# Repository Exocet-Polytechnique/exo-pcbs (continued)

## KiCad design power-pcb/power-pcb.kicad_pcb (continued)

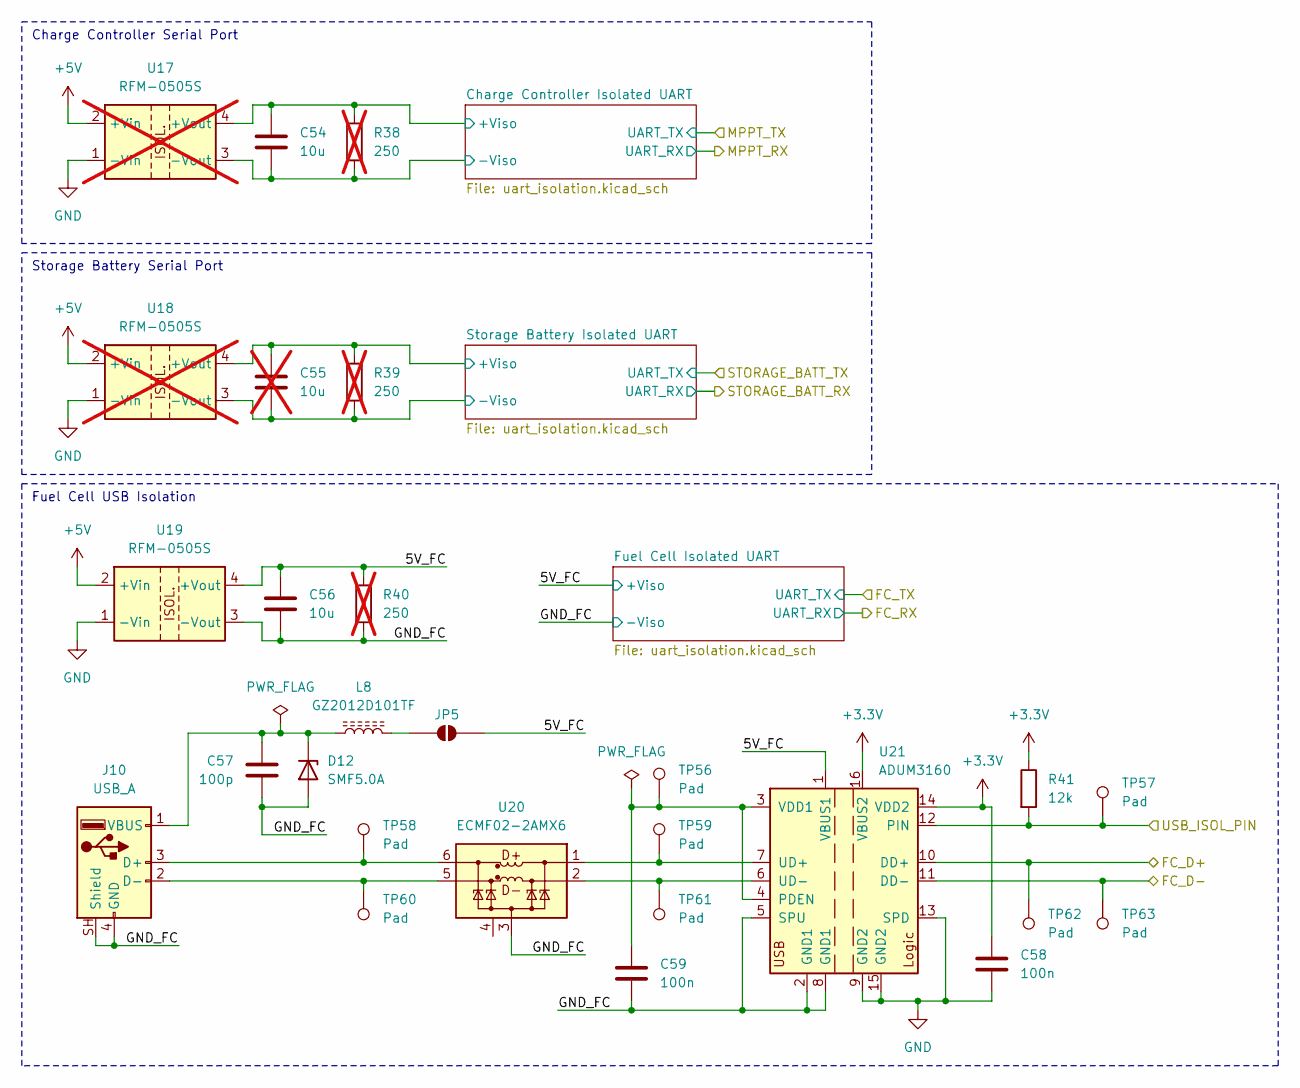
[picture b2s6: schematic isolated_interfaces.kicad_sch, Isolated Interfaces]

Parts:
C54, C56: 10u; C_1206_3216Metric_Pad1.33x1.80mm_HandSolder; JLCPCB C13585
C55: 10u; C_1206_3216Metric_Pad1.33x1.80mm_HandSolder; JLCPCB C13585; not fitted
C57: 100p; C_0402_1005Metric_Pad0.74x0.62mm_HandSolder; JLCPCB C1546
C58, C59: 100n; C_0402_1005Metric_Pad0.74x0.62mm_HandSolder; JLCPCB C307331
D12: SMF5.0A; D_SOD-123F; JLCPCB C19077497
J10: USB_A; USB_A_Molex_67643_Horizontal; MPN 0676430910
JP5: SolderJumper_2_Open; SolderJumper-2_P1.3mm_Open_RoundedPad1.0x1.5mm
L8: GZ2012D101TF; L_0805_2012Metric_Pad1.05x1.20mm_HandSolder; JLCPCB C1015
R38, R39, R40: 250; R_Axial_DIN0309_L9.0mm_D3.2mm_P12.70mm_Horizontal; MPN MFR-25FTE52-270R; not fitted
R41: 12k; R_0402_1005Metric_Pad0.72x0.64mm_HandSolder; JLCPCB C25752
TP56, TP57, TP58, TP59, TP60, TP61, TP62, TP63: Pad; TestPoint_Pad_D1.5mm
U17, U18: RFM-0505S; RECOM_SIP-4; MPN RFM-0505S; not fitted
U19: RFM-0505S; RECOM_SIP-4; MPN RFM-0505S
U20: ECMF02-2AMX6; ST_UQFN-6L_1.5x1.7mm_P0.5mm; JLCPCB C2651144
U21: ADUM3160; SOIC-16W_7.5x10.3mm_P1.27mm; MPN ADUM3160BRWZ; JLCPCB C284149

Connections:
+3.3V: C58.1, R41.1, U21.14 (VDD2), U21.16 (VBUS2); also elsewhere on the board
+5V: U17.2 (+Vin), U18.2 (+Vin), U19.2 (+Vin); also elsewhere on the board
/Isolated Interfaces/5V_FC: C56.1, JP5.2 (B), R40.1, U19.4 (+Vout), U21.1 (VBUS1); also elsewhere on the board
/Isolated Interfaces/Charge Controller Isolated UART/+Viso: C54.1, R38.1, U17.4 (+Vout); also elsewhere on the board
/Isolated Interfaces/Charge Controller Isolated UART/-Viso: C54.2, R38.2, U17.3 (-Vout); also elsewhere on the board
/Isolated Interfaces/FC_D+: TP62.1 (1_1), U21.10 (DD+); also elsewhere on the board
/Isolated Interfaces/FC_D-: TP63.1 (1_1), U21.11 (DD-); also elsewhere on the board
/Isolated Interfaces/GND_FC: C56.2, C57.2, C59.2, D12.2 (A), J10.4 (GND), J10.SH (Shield), R40.2, U19.3 (-Vout), U20.3 (GND), U21.2 (GND1), U21.5 (SPU), U21.8 (GND1); also elsewhere on the board
/Isolated Interfaces/Storage Battery Isolated UART/+Viso: C55.1, R39.1, U18.4 (+Vout); also elsewhere on the board
/Isolated Interfaces/Storage Battery Isolated UART/-Viso: C55.2, R39.2, U18.3 (-Vout); also elsewhere on the board
/Isolated Interfaces/USB_ISOL_PIN: R41.2, TP57.1 (1_1), U21.12 (PIN); also elsewhere on the board
GND: C58.2, U17.1 (-Vin), U18.1 (-Vin), U19.1 (-Vin), U21.9 (GND2), U21.13 (SPD), U21.15 (GND2); also elsewhere on the board
unnamed: C57.1, D12.1 (K), J10.1 (VBUS), L8.1
unnamed: J10.3 (D+), TP58.1 (1_1), U20.6 (D+_out)
unnamed: J10.2 (D-), TP60.1 (1_1), U20.5 (D-_out)
unnamed: JP5.1 (A), L8.2
unnamed: TP59.1 (1_1), U20.1 (D+_in), U21.7 (UD+)
unnamed: TP61.1 (1_1), U20.2 (D-_in), U21.6 (UD-)
unnamed: C59.1, TP56.1 (1_1), U21.3 (VDD1), U21.4 (PDEN)

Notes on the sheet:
Storage Battery Serial Port
Charge Controller Serial Port
Fuel Cell USB Isolation

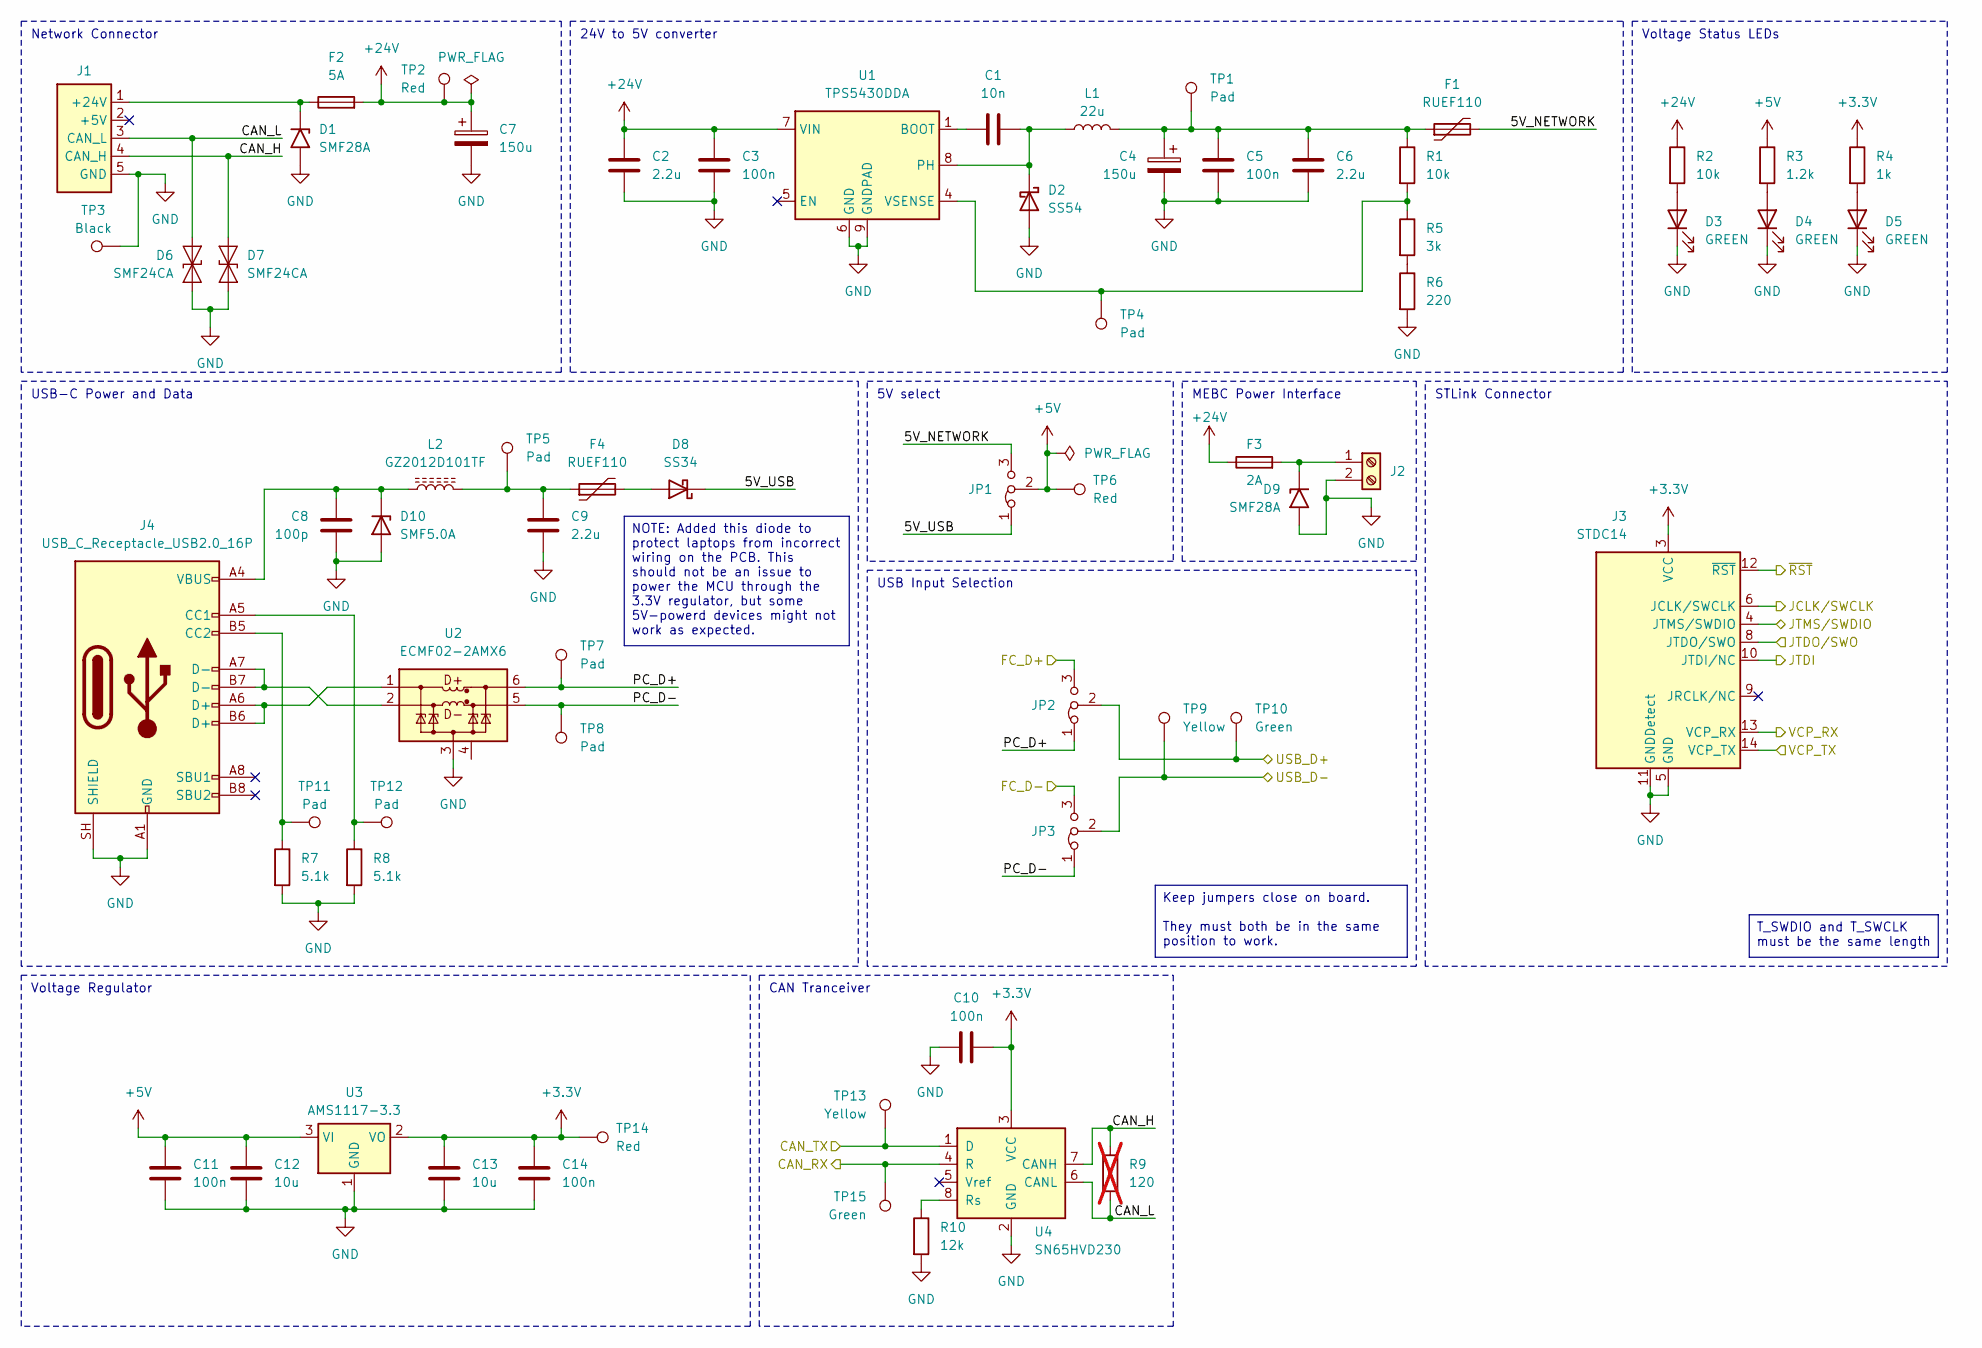
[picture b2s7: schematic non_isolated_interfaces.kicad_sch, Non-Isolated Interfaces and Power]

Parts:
C1: 10n; C_0402_1005Metric_Pad0.74x0.62mm_HandSolder; JLCPCB C15195
C2, C6, C9: 2.2u; C_0805_2012Metric_Pad1.18x1.45mm_HandSolder; JLCPCB C377773
C3, C5, C10, C11, C14: 100n; C_0402_1005Metric_Pad0.74x0.62mm_HandSolder; JLCPCB C307331
C4, C7: 150u; CP_Radial_D8.0mm_P3.50mm; MPN 860020574010
C8: 100p; C_0402_1005Metric_Pad0.74x0.62mm_HandSolder; JLCPCB C1546
C12, C13: 10u; C_1206_3216Metric_Pad1.33x1.80mm_HandSolder; JLCPCB C13585
D1, D9: SMF28A; D_SMF; JLCPCB C41376091
D2: SS54; D_SMA_Handsoldering; JLCPCB C22452
D3, D4, D5: GREEN; LED_0805_2012Metric_With_Annotations; JLCPCB C2297
D6, D7: SMF24CA; D_SOD-123F; JLCPCB C19077515
D8: SS34; D_SMA; JLCPCB C8678
D10: SMF5.0A; D_SOD-123F; JLCPCB C19077497
F1, F4: RUEF110; Fuse_Littelfuse_395Series; MPN RUEF110
F2: 5A; Fuseholder_Littelfuse_Combined; MPN 01110501Z
F3: 2A; Fuseholder_Littelfuse_Combined; MPN 01110501Z
J1: Network Connector; Molex_SPOX_5268-05A_1x05_P2.50mm_Horizontal; MPN 0022057055
J2: Screw_Terminal_01x02; Wuerth_Term_Blk_2pos_Side_Entry_5mm; MPN 691137710002
J3: STDC14; PinHeader_2x07_P1.27mm_Vertical_SMD; JLCPCB C7465995
J4: USB_C_Receptacle_USB2.0_16P; USB_C_Receptacle_GCT_USB4085; MPN USB4920-00-A
JP1, JP2, JP3: Jumper_3_Bridged12; PinHeader_1x03_P2.54mm_Vertical; MPN PR20203VBNN
L1: 22u; L_Axial_L16.0mm_D6.3mm_P5.08mm_Vertical_Fastron_VHBCC; MPN AIAP-02-220K
L2: GZ2012D101TF; L_0805_2012Metric_Pad1.05x1.20mm_HandSolder; JLCPCB C1015
R1, R2: 10k; R_0805_2012Metric_Pad1.20x1.40mm_HandSolder; JLCPCB C17414
R3: 1.2k; R_0603_1608Metric_Pad0.98x0.95mm_HandSolder; JLCPCB C22765
R4: 1k; R_0603_1608Metric_Pad0.98x0.95mm_HandSolder; JLCPCB C21190
R5: 3k; R_0603_1608Metric_Pad0.98x0.95mm_HandSolder; JLCPCB C4211
R6: 220; R_0402_1005Metric_Pad0.72x0.64mm_HandSolder; JLCPCB C25091
R7, R8: 5.1k; R_0402_1005Metric_Pad0.72x0.64mm_HandSolder; JLCPCB C25905
R9: 120; R_Axial_DIN0309_L9.0mm_D3.2mm_P12.70mm_Horizontal; MPN CF12JT120R; not fitted
R10: 12k; R_0402_1005Metric_Pad0.72x0.64mm_HandSolder; JLCPCB C25752
TP1, TP4, TP5, TP7, TP8, TP11, TP12: Pad; TestPoint_Pad_D1.5mm
TP2, TP6, TP14: Red; TestPoint_Keystone_5005-5009_Compact; MPN 5005
TP3: Black; TestPoint_Keystone_5005-5009_Compact; MPN 5006
TP9, TP13: Yellow; TestPoint_Keystone_5005-5009_Compact; MPN 5009
TP10, TP15: Green; TestPoint_Keystone_5005-5009_Compact; MPN 5121
U1: TPS5430DDA; TI_SO-PowerPAD-8_ThermalVias; JLCPCB C9864
U2: ECMF02-2AMX6; ST_UQFN-6L_1.5x1.7mm_P0.5mm; JLCPCB C2651144
U3: AMS1117-3.3; SOT-223-3_TabPin2; JLCPCB C6186
U4: SN65HVD230; SOIC-8_3.9x4.9mm_P1.27mm; JLCPCB C12084

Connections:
+3.3V: C10.1, C13.1, C14.1, J3.3 (VCC), R4.1, TP14.1 (1_1), U3.2 (VO), U4.3 (VCC); also elsewhere on the board
+5V: C11.1, C12.1, JP1.2 (C), R3.1, TP6.1 (1_1), U3.3 (VI); also elsewhere on the board
+24V: C2.2, C3.1, C7.1, F2.2, F3.1, R2.1, TP2.1 (1_1), U1.7 (VIN); also elsewhere on the board
/Isolated Interfaces/FC_D+: JP2.3 (B); also elsewhere on the board
/Isolated Interfaces/FC_D-: JP3.3 (B); also elsewhere on the board
/Non-Isolated Interfaces and Power/5V_NETWORK: F1.2, JP1.3 (B)
/Non-Isolated Interfaces and Power/5V_USB: D8.1 (K), JP1.1 (A)
/Non-Isolated Interfaces and Power/CAN_H: D7.2 (A2), J1.4 (CAN_H), R9.1, U4.7 (CANH)
/Non-Isolated Interfaces and Power/CAN_L: D6.2 (A2), J1.3 (CAN_L), R9.2, U4.6 (CANL)
/Non-Isolated Interfaces and Power/CAN_RX: TP15.1 (1_1), U4.4 (R); also elsewhere on the board
/Non-Isolated Interfaces and Power/CAN_TX: TP13.1 (1_1), U4.1 (D); also elsewhere on the board
/Non-Isolated Interfaces and Power/JCLK/SWCLK: J3.6 (JCLK/SWCLK); also elsewhere on the board
/Non-Isolated Interfaces and Power/JTDI: J3.10 (JTDI/NC); also elsewhere on the board
/Non-Isolated Interfaces and Power/JTDO/SWO: J3.8 (JTDO/SWO); also elsewhere on the board
/Non-Isolated Interfaces and Power/JTMS/SWDIO: J3.4 (JTMS/SWDIO); also elsewhere on the board
/Non-Isolated Interfaces and Power/PC_D+: JP2.1 (A), TP7.1 (1_1), U2.6 (D+_out)
/Non-Isolated Interfaces and Power/PC_D-: JP3.1 (A), TP8.1 (1_1), U2.5 (D-_out)
/Non-Isolated Interfaces and Power/USB_D+: JP2.2 (C), TP10.1 (1_1); also elsewhere on the board
/Non-Isolated Interfaces and Power/USB_D-: JP3.2 (C), TP9.1 (1_1); also elsewhere on the board
/Non-Isolated Interfaces and Power/VCP_RX: J3.13 (VCP_RX); also elsewhere on the board
/Non-Isolated Interfaces and Power/VCP_TX: J3.14 (VCP_TX); also elsewhere on the board
/Non-Isolated Interfaces and Power/~RST: J3.12 (~RST); also elsewhere on the board
GND: C2.1, C3.2, C4.2, C5.2, C6.1, C7.2, C8.2, C9.2, C10.2, C11.2, C12.2, C13.2, C14.2, D1.2 (A2), D2.2 (A), D3.1 (K), D4.1 (K), D5.1 (K), D6.1 (A1), D7.1 (A1), D9.2 (A2), D10.2 (A), J1.5 (GND), J2.2, J3.5 (GND), J3.7 (GND), J3.11 (GNDDetect), J4.A1 (GND), J4.A12 (GND), J4.B1 (GND), J4.B12 (GND), J4.SH (SHIELD), R6.2, R7.2, R8.2, R10.2, TP3.1 (1_1), U1.6 (GND), U1.9 (GNDPAD), U2.3 (GND), U3.1 (GND), U4.2 (GND); also elsewhere on the board
unnamed: C4.1, C5.1, C6.2, F1.1, L1.2, R1.1, TP1.1 (1_1)
unnamed: C9.1, F4.1, L2.2, TP5.1 (1_1)
unnamed: D1.1 (A1), F2.1, J1.1 (+24V)
unnamed: C1.2, D2.1 (K), L1.1, U1.8 (PH)
unnamed: D3.2 (A), R2.2
unnamed: D4.2 (A), R3.2
unnamed: D5.2 (A), R4.2
unnamed: D8.2 (A), F4.2
unnamed: D9.1 (A1), F3.2, J2.1
unnamed: C8.1, D10.1 (K), J4.A4 (VBUS), J4.A9 (VBUS), J4.B4 (VBUS), J4.B9 (VBUS), L2.1
unnamed: J4.A5 (CC1), R8.1, TP12.1 (1_1)
unnamed: J4.B5 (CC2), R7.1, TP11.1 (1_1)
unnamed: R5.2, R6.1
unnamed: C1.1, U1.1 (BOOT)
unnamed: R1.2, R5.1, TP4.1 (1_1), U1.4 (VSENSE)
unnamed: J4.A6 (D+), J4.B6 (D+), U2.1 (D+_in)
unnamed: J4.A7 (D-), J4.B7 (D-), U2.2 (D-_in)
unnamed: R10.1, U4.8 (Rs)

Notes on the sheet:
Voltage Regulator
CAN Tranceiver
5V select
USB-C Power and Data
MEBC Power Interface
USB Input Selection
Network Connector
24V to 5V converter
STLink Connector
Voltage Status LEDs
NOTE: Added this diode to protect laptops from incorrect wiring on the PCB. This should not be an issue to power the MCU through the 3.3V regulator, but some 5V-powerd devices might not work as expected.
T_SWDIO and T_SWCLK must be the same length
Keep jumpers close on board. They must both be in the same position to work.

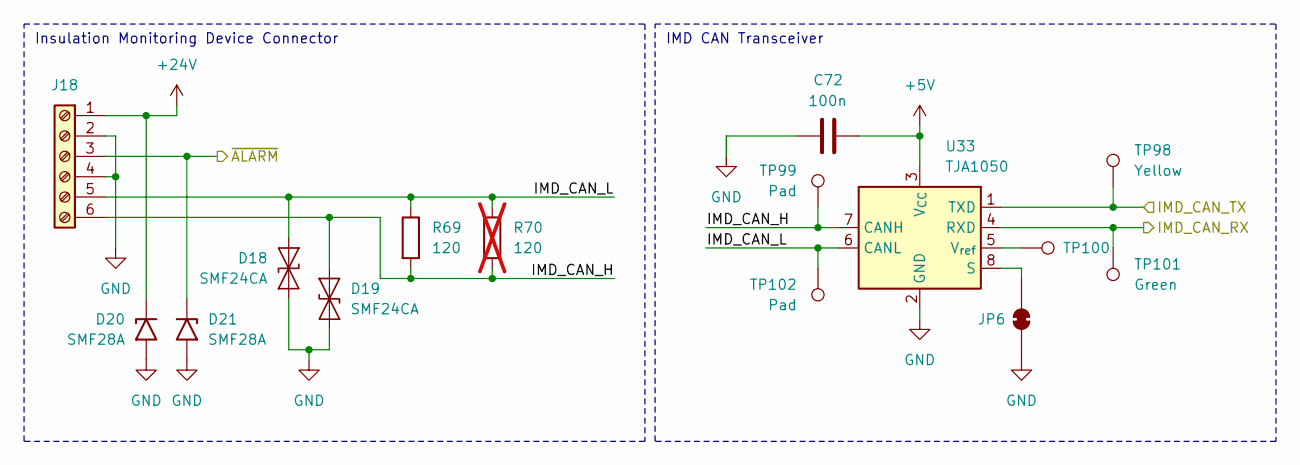
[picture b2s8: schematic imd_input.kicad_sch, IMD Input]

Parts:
C72: 100n; C_0402_1005Metric_Pad0.74x0.62mm_HandSolder; JLCPCB C307331
D18, D19: SMF24CA; D_SOD-123F; JLCPCB C19077515
D20, D21: SMF28A; D_SMF; JLCPCB C41376091
J18: Screw_Terminal_01x06; Wuerth_Term_Blk_6pos_Side_Entry_5mm; MPN 691137710006
JP6: SolderJumper_2_Bridged; SolderJumper-2_P1.3mm_Bridged_Pad1.0x1.5mm
R69: 120; R_Axial_DIN0309_L9.0mm_D3.2mm_P12.70mm_Horizontal; MPN CF12JT120R
R70: 120; R_Axial_DIN0309_L9.0mm_D3.2mm_P12.70mm_Horizontal; MPN CF12JT120R; not fitted
TP98: Yellow; TestPoint_Keystone_5005-5009_Compact; MPN 5009
TP99, TP102: Pad; TestPoint_Pad_D1.5mm
TP100: Hole; TestPoint_THTPad_D2.0mm_Drill1.0mm
TP101: Green; TestPoint_Keystone_5005-5009_Compact; MPN 5121
U33: TJA1050; SOIC-8_3.9x4.9mm_P1.27mm; JLCPCB C6952

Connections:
+5V: C72.2, U33.3 (V_{CC}); also elsewhere on the board
+24V: D20.1 (A1), J18.1; also elsewhere on the board
/STM32 Microcontroller/IMD_CAN_RX: TP101.1 (1_1), U33.4 (RXD); also elsewhere on the board
/STM32 Microcontroller/IMD_CAN_TX: TP98.1 (1_1), U33.1 (TXD); also elsewhere on the board
/Safety Systems/IMD Input/IMD_CAN_H: D19.2 (A2), J18.6, R69.2, R70.2, TP99.1 (1_1), U33.7 (CANH)
/Safety Systems/IMD Input/IMD_CAN_L: D18.2 (A2), J18.5, R69.1, R70.1, TP102.1 (1_1), U33.6 (CANL)
/Safety Systems/~ALARM: D21.1 (A1), J18.3; also elsewhere on the board
GND: C72.1, D18.1 (A1), D19.1 (A1), D20.2 (A2), D21.2 (A2), J18.2, J18.4, JP6.1 (A), U33.2 (GND); also elsewhere on the board
unnamed: JP6.2 (B), U33.8 (S)
unnamed: TP100.1 (1_1), U33.5 (V_{ref})

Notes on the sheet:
Insulation Monitoring Device Connector
IMD CAN Transceiver

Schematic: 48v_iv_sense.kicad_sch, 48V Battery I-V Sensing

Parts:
C40, C41, C42: 100n; C_0402_1005Metric_Pad0.74x0.62mm_HandSolder; JLCPCB C307331
C43, C44, C45, C46: 10n; C_0402_1005Metric_Pad0.74x0.62mm_HandSolder; JLCPCB C15195
J8: Screw_Terminal_01x03; Wuerth_Term_Blk_3pos_Side_Entry_5mm; MPN 691137710003
L4, L5: GZ2012D101TF; L_0805_2012Metric_Pad1.05x1.20mm_HandSolder; JLCPCB C1015
R20: 56k; R_0603_1608Metric_Pad0.98x0.95mm_HandSolder; JLCPCB C23206
R21: 5.1k; R_0402_1005Metric_Pad0.72x0.64mm_HandSolder; JLCPCB C25905
R22, R23, R24, R25: 12k; R_0402_1005Metric_Pad0.72x0.64mm_HandSolder; JLCPCB C25752
R26, R27: 2.7k; R_0603_1608Metric_Pad0.98x0.95mm_HandSolder; JLCPCB C13167
R28: 100; R_0603_1608Metric_Pad0.98x0.95mm_HandSolder; JLCPCB C22775
TP42, TP46, TP48: Hole; TestPoint_THTPad_D2.0mm_Drill1.0mm
TP43, TP45: Pad; TestPoint_Pad_D1.5mm
TP44: Yellow; TestPoint_Keystone_5005-5009_Compact; MPN 5009
TP47: Green; TestPoint_Keystone_5005-5009_Compact; MPN 5121
U9: MCP6002T; SOIC-8_3.9x4.9mm_P1.27mm; MPN MCP6002T-I/SN; JLCPCB C7377
U10: INA240A1D; SOIC-8_3.9x4.9mm_P1.27mm; JLCPCB C2060769
U11: ADS1015IDGS; TSSOP-10_3x3mm_P0.5mm; JLCPCB C193969
U12: ISO1540; SOIC-8_3.9x4.9mm_P1.27mm; JLCPCB C179739

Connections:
+3.3V: U12.1 (VCC1); also elsewhere on the board
/Battery Sensing/Auxiliary Battery I-V Sensing/5V_ISO: C41.1, L4.1, L5.1, R26.1, R27.1, U9.8 (V+), U12.8 (VCC2); also elsewhere on the board
/Battery Sensing/Auxiliary Battery I-V Sensing/ADDR: C40.2, C41.2, C42.2, C43.2, C44.2, C45.2, C46.2, J8.3, R21.1, R23.1, R25.1, R28.1, U9.4 (V-), U10.2 (GND), U10.4 (GND), U10.7 (REF1), U11.3 (GND), U12.5 (GND2); also elsewhere on the board
/Battery Sensing/Auxiliary Battery I-V Sensing/I_SENSE: C43.1, TP43.1 (1_1), U10.5, U11.4 (AIN0)
/Battery Sensing/Auxiliary Battery I-V Sensing/SENSE+: J8.1, R22.1
/Battery Sensing/Auxiliary Battery I-V Sensing/SENSE-: J8.2, R20.1, R24.1
/Battery Sensing/Auxiliary Battery I-V Sensing/V_SENSE: C44.1, TP45.1 (1_1), U9.1, U9.2 (-), U11.5 (AIN1)
/Battery Sensing/SCL: U12.3 (SCL1); also elsewhere on the board
/Battery Sensing/SDA: U12.2 (SDA1); also elsewhere on the board
GND: U12.4 (GND1); also elsewhere on the board
unnamed: TP42.1 (1_1), U9.7
unnamed: R20.2, R21.2, U9.3 (+)
unnamed: R23.2, U9.5 (+)
unnamed: R25.2, U9.6 (-)
unnamed: R22.2, U10.8 (+)
unnamed: R24.2, U10.1 (-)
unnamed: C40.1, L4.2, U10.3 (REF2), U10.6 (V+)
unnamed: R28.2, U11.1 (ADDR)
unnamed: C45.1, TP46.1 (1_1), U11.6 (AIN2)
unnamed: C46.1, TP48.1 (1_1), U11.7 (AIN3)
unnamed: R26.2, TP44.1 (1_1), U11.10 (SCL), U12.6 (SCL2)
unnamed: R27.2, TP47.1 (1_1), U11.9 (SDA), U12.7 (SDA2)
unnamed: C42.1, L5.2, U11.8 (VDD)

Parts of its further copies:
C47, C48, C49: 100n; C_0402_1005Metric_Pad0.74x0.62mm_HandSolder; JLCPCB C307331
C50, C51, C52, C53: 10n; C_0402_1005Metric_Pad0.74x0.62mm_HandSolder; JLCPCB C15195
J9: Screw_Terminal_01x03; Wuerth_Term_Blk_3pos_Side_Entry_5mm; MPN 691137710003
L6, L7: GZ2012D101TF; L_0805_2012Metric_Pad1.05x1.20mm_HandSolder; JLCPCB C1015
R29: 56k; R_0603_1608Metric_Pad0.98x0.95mm_HandSolder; JLCPCB C23206
R30: 5.1k; R_0402_1005Metric_Pad0.72x0.64mm_HandSolder; JLCPCB C25905
R31, R32, R33, R34: 12k; R_0402_1005Metric_Pad0.72x0.64mm_HandSolder; JLCPCB C25752
R35, R36: 2.7k; R_0603_1608Metric_Pad0.98x0.95mm_HandSolder; JLCPCB C13167
R37: 100; R_0603_1608Metric_Pad0.98x0.95mm_HandSolder; JLCPCB C22775
TP49, TP53, TP55: Hole; TestPoint_THTPad_D2.0mm_Drill1.0mm
TP50, TP52: Pad; TestPoint_Pad_D1.5mm
TP51: Yellow; TestPoint_Keystone_5005-5009_Compact; MPN 5009
TP54: Green; TestPoint_Keystone_5005-5009_Compact; MPN 5121
U13: MCP6002T; SOIC-8_3.9x4.9mm_P1.27mm; MPN MCP6002T-I/SN; JLCPCB C7377
U14: INA240A1D; SOIC-8_3.9x4.9mm_P1.27mm; JLCPCB C2060769
U15: ADS1015IDGS; TSSOP-10_3x3mm_P0.5mm; JLCPCB C193969
U16: ISO1540; SOIC-8_3.9x4.9mm_P1.27mm; JLCPCB C179739

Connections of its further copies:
+3.3V: U16.1 (VCC1); also elsewhere on the board
/Battery Sensing/SCL: U16.3 (SCL1); also elsewhere on the board
/Battery Sensing/SDA: U16.2 (SDA1); also elsewhere on the board
/Battery Sensing/Storage Battery I-V Sensing/5V_ISO: C48.1, L6.1, L7.1, R35.1, R36.1, R37.1, U13.8 (V+), U16.8 (VCC2); also elsewhere on the board
/Battery Sensing/Storage Battery I-V Sensing/GND_ISO: C47.2, C48.2, C49.2, C50.2, C51.2, C52.2, C53.2, J9.3, R30.1, R32.1, R34.1, U13.4 (V-), U14.2 (GND), U14.4 (GND), U14.7 (REF1), U15.3 (GND), U16.5 (GND2); also elsewhere on the board
/Battery Sensing/Storage Battery I-V Sensing/I_SENSE: C50.1, TP50.1 (1_1), U14.5, U15.4 (AIN0)
/Battery Sensing/Storage Battery I-V Sensing/SENSE+: J9.1, R31.1
/Battery Sensing/Storage Battery I-V Sensing/SENSE-: J9.2, R29.1, R33.1
/Battery Sensing/Storage Battery I-V Sensing/V_SENSE: C51.1, TP52.1 (1_1), U13.1, U13.2 (-), U15.5 (AIN1)
GND: U16.4 (GND1); also elsewhere on the board
unnamed: TP49.1 (1_1), U13.7
unnamed: R29.2, R30.2, U13.3 (+)
unnamed: R32.2, U13.5 (+)
unnamed: R34.2, U13.6 (-)
unnamed: R31.2, U14.8 (+)
unnamed: R33.2, U14.1 (-)
unnamed: C47.1, L6.2, U14.3 (REF2), U14.6 (V+)
unnamed: R37.2, U15.1 (ADDR)
unnamed: C52.1, TP53.1 (1_1), U15.6 (AIN2)
unnamed: C53.1, TP55.1 (1_1), U15.7 (AIN3)
unnamed: R35.2, TP51.1 (1_1), U15.10 (SCL), U16.6 (SCL2)
unnamed: R36.2, TP54.1 (1_1), U15.9 (SDA), U16.7 (SDA2)
unnamed: C49.1, L7.2, U15.8 (VDD)

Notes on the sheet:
Current Sensing (using external 0.75 mΩ shunt)
I2C Isolation
ADC
Input Connector (~ 48V)
Voltage Sensing (~ 48V -> 5V)

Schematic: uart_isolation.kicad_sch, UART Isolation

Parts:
C60, C61: 100n; C_0402_1005Metric_Pad0.74x0.62mm_HandSolder; JLCPCB C307331
J11: Screw_Terminal_01x04; Wuerth_Term_Blk_4pos_Side_Entry_5mm; MPN 691137710004
TP64, TP65: Yellow; TestPoint_Keystone_5005-5009_Compact; MPN 5009
TP66, TP67: Green; TestPoint_Keystone_5005-5009_Compact; MPN 5121
U22: ADUM1201AR; SOIC-8_3.9x4.9mm_P1.27mm; JLCPCB C9669
U23: SRV05-4; SOT-23-6; JLCPCB C7420376

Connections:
+3.3V: C61.1, U22.8 (VDD2); also elsewhere on the board
/Isolated Interfaces/5V_FC: C60.1, J11.1, U22.1 (VDD1), U23.5 (VP); also elsewhere on the board
/Isolated Interfaces/FC_RX: TP67.1 (1_1), U22.6 (VOB); also elsewhere on the board
/Isolated Interfaces/FC_TX: TP64.1 (1_1), U22.7 (VIA); also elsewhere on the board
/Isolated Interfaces/Fuel Cell Isolated UART/RX_ISO: J11.2, TP65.1 (1_1), U22.2 (VOA), U23.1 (IO1)
/Isolated Interfaces/Fuel Cell Isolated UART/TX_ISO: J11.3, TP66.1 (1_1), U22.3 (VIB), U23.3 (IO2)
/Isolated Interfaces/GND_FC: C60.2, J11.4, U22.4 (GND1), U23.2 (VN); also elsewhere on the board
GND: C61.2, U22.5 (GND2); also elsewhere on the board

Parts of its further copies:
C62, C63, C64, C65: 100n; C_0402_1005Metric_Pad0.74x0.62mm_HandSolder; JLCPCB C307331
J12, J13: Screw_Terminal_01x04; Wuerth_Term_Blk_4pos_Side_Entry_5mm; MPN 691137710004
TP68, TP69, TP72, TP73: Yellow; TestPoint_Keystone_5005-5009_Compact; MPN 5009
TP70, TP71, TP74, TP75: Green; TestPoint_Keystone_5005-5009_Compact; MPN 5121
U24, U26: ADUM1201AR; SOIC-8_3.9x4.9mm_P1.27mm; JLCPCB C9669
U25, U27: SRV05-4; SOT-23-6; JLCPCB C7420376

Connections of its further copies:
+3.3V: C63.1, C65.1, U24.8 (VDD2), U26.8 (VDD2); also elsewhere on the board
/Isolated Interfaces/Charge Controller Isolated UART/+Viso: C62.1, J12.1, U24.1 (VDD1), U25.5 (VP); also elsewhere on the board
/Isolated Interfaces/Charge Controller Isolated UART/-Viso: C62.2, J12.4, U24.4 (GND1), U25.2 (VN); also elsewhere on the board
/Isolated Interfaces/Charge Controller Isolated UART/RX_ISO: J12.2, TP69.1 (1_1), U24.2 (VOA), U25.1 (IO1)
/Isolated Interfaces/Charge Controller Isolated UART/TX_ISO: J12.3, TP70.1 (1_1), U24.3 (VIB), U25.3 (IO2)
/Isolated Interfaces/MPPT_RX: TP71.1 (1_1), U24.6 (VOB); also elsewhere on the board
/Isolated Interfaces/MPPT_TX: TP68.1 (1_1), U24.7 (VIA); also elsewhere on the board
/Isolated Interfaces/STORAGE_BATT_RX: TP75.1 (1_1), U26.6 (VOB); also elsewhere on the board
/Isolated Interfaces/STORAGE_BATT_TX: TP72.1 (1_1), U26.7 (VIA); also elsewhere on the board
/Isolated Interfaces/Storage Battery Isolated UART/+Viso: C64.1, J13.1, U26.1 (VDD1), U27.5 (VP); also elsewhere on the board
/Isolated Interfaces/Storage Battery Isolated UART/-Viso: C64.2, J13.4, U26.4 (GND1), U27.2 (VN); also elsewhere on the board
/Isolated Interfaces/Storage Battery Isolated UART/RX_ISO: J13.2, TP73.1 (1_1), U26.2 (VOA), U27.1 (IO1)
/Isolated Interfaces/Storage Battery Isolated UART/TX_ISO: J13.3, TP74.1 (1_1), U26.3 (VIB), U27.3 (IO2)
GND: C63.2, C65.2, U24.5 (GND2), U26.5 (GND2); also elsewhere on the board

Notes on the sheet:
UART Isolation
Input Connector and ESD Protection

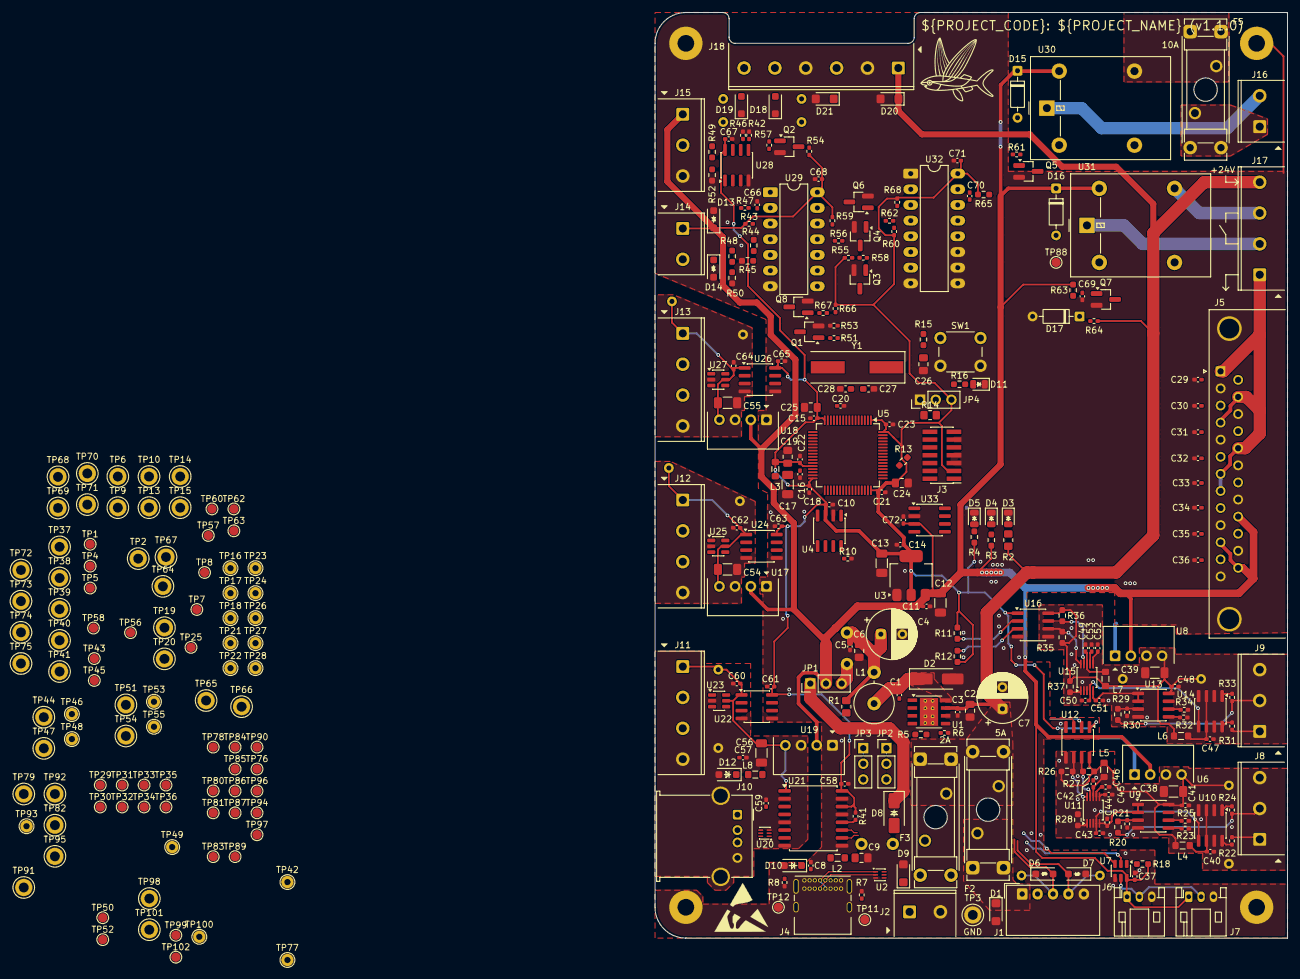
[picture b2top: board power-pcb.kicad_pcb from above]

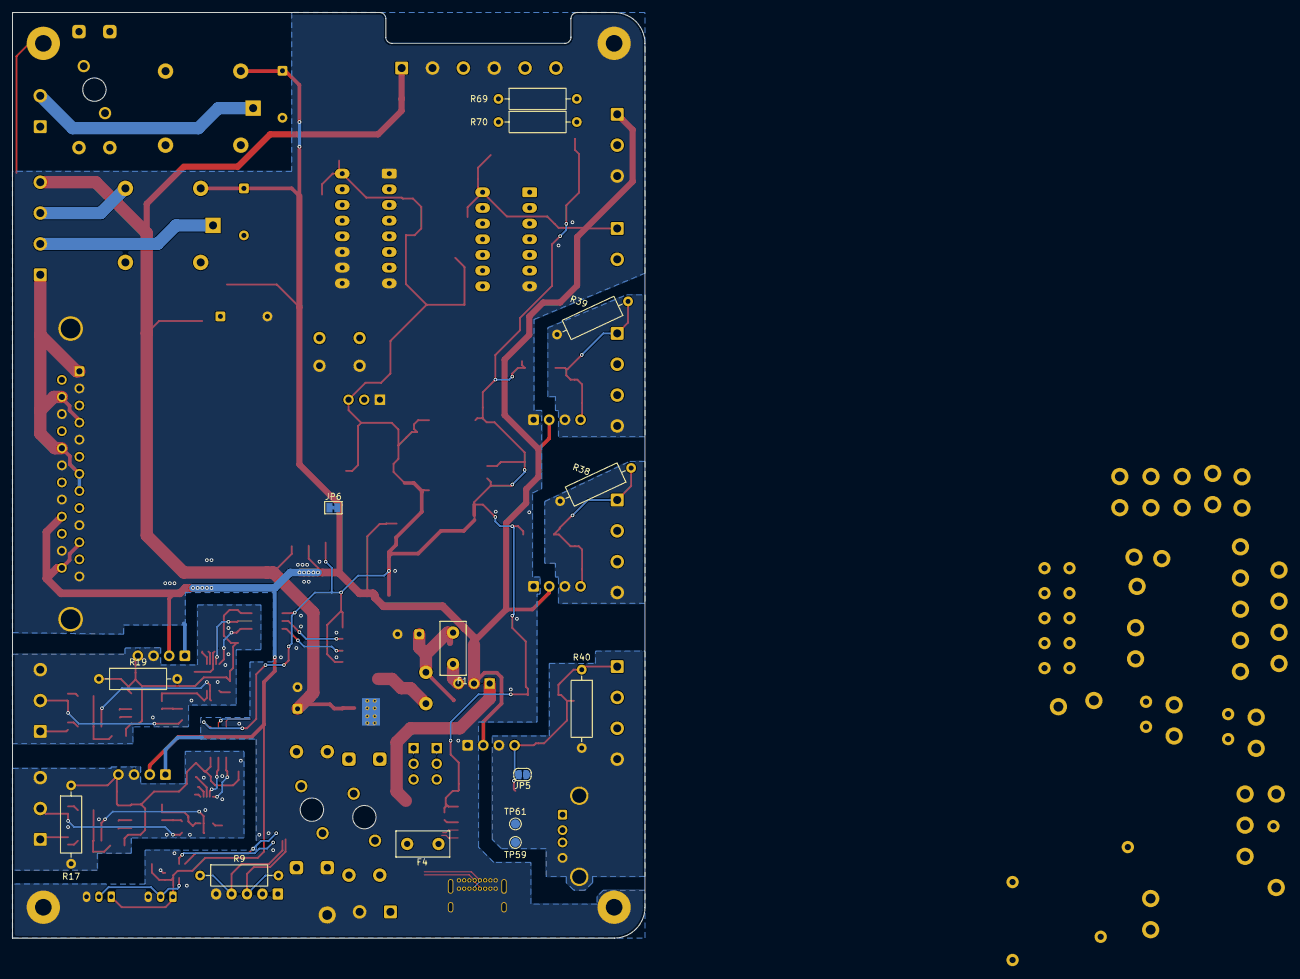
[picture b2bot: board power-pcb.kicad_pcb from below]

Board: 2 copper layers, 102.5 x 150.0 mm, 350 parts (14 on the bottom side), 184 nets.

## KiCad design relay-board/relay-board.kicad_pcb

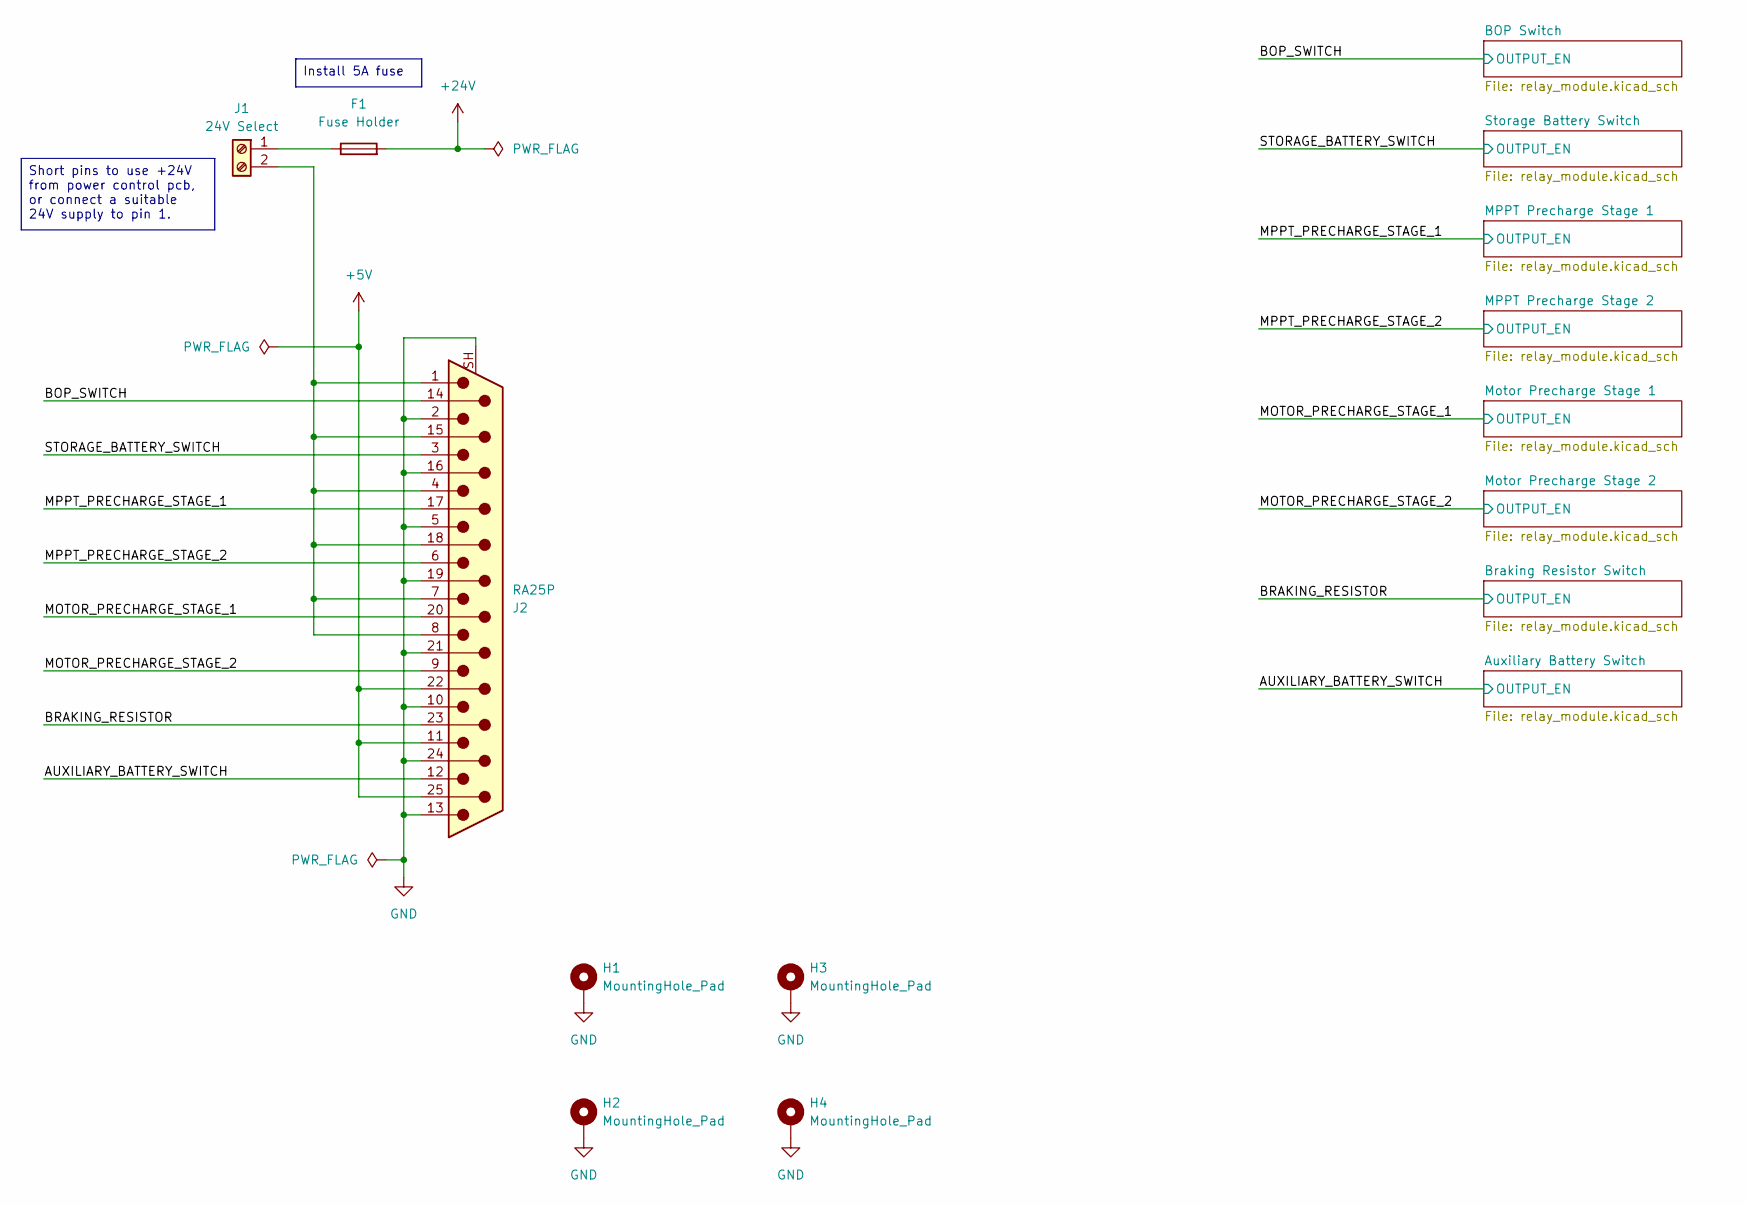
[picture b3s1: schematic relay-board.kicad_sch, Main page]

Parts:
F1: Fuse Holder; Fuseholder_Clip-5x20mm_Littelfuse_111_Lateral_P18.80x5.00mm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; MPN 01110501Z
H1, H2, H3, H4: MountingHole_Pad; MountingHole_2.7mm_Pad
J1: 24V Select; Wurth_Term_Blk_2pos_Side_Entry_5mm; MPN 691137710002
J2: RA25P; DSUB-25_Pins_Horizontal_P2.77x2.84mm_EdgePinOffset7.70mm_Ho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

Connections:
+5V: J2.11, J2.22, J2.25; also elsewhere on the board
+24V: F1.2; also elsewhere on the board
/AUXILIARY_BATTERY_SWITCH: J2.12; also elsewhere on the board
/BOP_SWITCH: J2.14; also elsewhere on the board
/BRAKING_RESISTOR: J2.23; also elsewhere on the board
/MOTOR_PRECHARGE_STAGE_1: J2.20; also elsewhere on the board
/MOTOR_PRECHARGE_STAGE_2: J2.9; also elsewhere on the board
/MPPT_PRECHARGE_STAGE_1: J2.17; also elsewhere on the board
/MPPT_PRECHARGE_STAGE_2: J2.6; also elsewhere on the board
/STORAGE_BATTERY_SWITCH: J2.3; also elsewhere on the board
GND: H1.1 (1_1), H2.1 (1_1), H3.1 (1_1), H4.1 (1_1), J2.2, J2.5, J2.10, J2.13, J2.16, J2.19, J2.21, J2.24, J2.SH (PAD); also elsewhere on the board
unnamed: F1.1, J1.1
unnamed: J1.2, J2.1, J2.4, J2.7, J2.8, J2.15, J2.18

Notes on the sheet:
Short pins to use +24V from power control pcb, or connect a suitable 24V supply to pin 1.
Install 5A fuse
